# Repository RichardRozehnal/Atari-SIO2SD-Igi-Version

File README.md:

# Atari SIO2SD Igi Version

SIO2SD je zařízení, které vám umožní nahrávat programy a hry do Atari přes SIO konektor z SD/MMC karty.

## Seznam součástek:

| Ref                      | Qnty | Value                       | Cmp name                    |
|--------------------------|:----:|-----------------------------|-----------------------------|
| C1, C2,                  | 2    | 22pF                        | C_1206                      |
| C9, C8, C7, C6, C5, C4,  | 6    | 22nF                        | C_1206                      |
| C11, C13, C12,           | 3    | 10uF                        | C_Tantal_A/3216             |
| C14, C3, C10,            | 3    | 100nF                       | C_1206                      |
| D1,                      | 1    | LED_Zelená                  | LED_5mm_Zelená              |
| D2,                      | 1    | LED_Žlutá                   | LED_5mm_Žlutá               |
| D3,                      | 1    | LED_Červená                 | LED_5mm_Červená             |
| D4,                      | 1    | LL103A                      | LL103A                      |
| K1,                      | 1    | DRIVE                       | Mikrospínač_6x6x5mm         |
| K2,                      | 1    | NEXT                        | Mikrospínač_6x6x5mm         |
| K3,                      | 1    | CD..                        | Mikrospínač_6x6x5mm         |
| K4,                      | 1    | ENTER                       | Mikrospínač_6x6x5mm         |
| K5,                      | 1    | SHIFT                       | Mikrospínač_6x6x5mm         |
| K6,                      | 1    | RESET                       | Mikrospínač_6x6x5mm         |
| K7,                      | 1    | KF2510-5_Angled_Pitch2.54mm | KF2510-5_Angled_Pitch2.54mm |
| K8,                      | 1    | SD_Card                     | SD_Card                     |
| LCD1,                    | 1    | Display_16x2                | Display_16x2                |
| P1,                      | 1    | 5k                          | 3362P                       |
| R1, R3, R13,             | 3    | 10k                         | R_1206                      |
| R2,                      | 1    | 27R                         | R_1206                      |
| R4, R6, R5,              | 3    | 220R                        | R_1206                      |
| R9, R8, R7,              | 3    | 1k8                         | R_1206                      |
| R11, R12, R10,           | 3    | 3k3                         | R_1206                      |
| U1,                      | 1    | ATMEGA32A-AU                | ATMEGA32A-AU                |
| U2,                      | 1    | HT7533-1                    | HT7533-1                    |
| WP1,                     | 1    | MOSI                        | Wire_Pad                    |
| WP2,                     | 1    | MISO                        | Wire_Pad                    |
| WP3,                     | 1    | SCK                         | Wire_Pad                    |
| WP4,                     | 1    | RST                         | Wire_Pad                    |
| Y1,                      | 1    | 14.318MHz                   | Krystal_HC49-U_Vertical     |

## Fotky hotového výrobku (DPS verze 1):

## Původní autoři zařízení jsou:

Device inventor and AVR software developer: Jakub Kruszona-Zawadzki<br>
ATARI software developer and tester: Paweł Nowak (Pajero/MadTeam)<br>
NVC developer: Marcin Sochacki (Montezuma)<br>
Tester (also new SMD PCB designer - still not finished): Jakub Husak<br>

Tato verze má vylepšené a zjednodušené zapojení od [Igiho](http://blog.3b2.sk/igi/post/SIO2SD-3verzia.aspx).
Otestováno na Atari 800XE a vše funguje bez problému.

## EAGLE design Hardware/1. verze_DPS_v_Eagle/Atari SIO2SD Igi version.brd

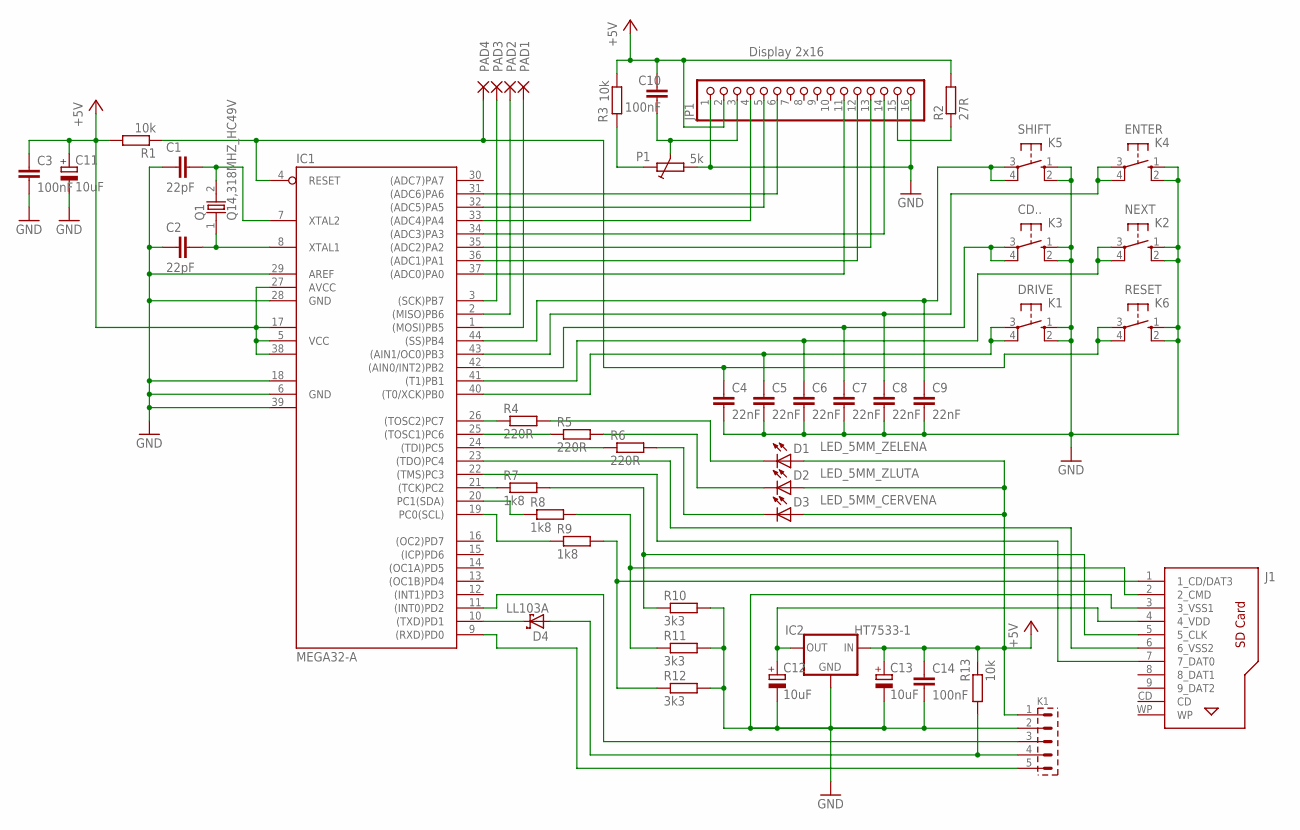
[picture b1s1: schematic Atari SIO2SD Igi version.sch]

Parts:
C1, C2: 22pF; 1206
C3, C10, C14: 100nF; 1206
C4, C5, C6, C7, C8, C9: 22nF; 1206
C11, C12, C13: 10uF; A/3216
CD..: K3; B3F-10XX
D1: LED_5MM_ZELENA; A5,0
D2: LED_5MM_ZLUTA; A5,0
D3: LED_5MM_CERVENA; A5,0
D4: LL103A; MINIMELF
DRIVE: K1; B3F-10XX
ENTER: K4; B3F-10XX
IC1: MEGA32-A; TQFP44
IC2: HT7533-1; SOT89R
J1: 693061010911
JP1: Display 2x16; 1X16
K1: PSH02-05W
NEXT: K2; B3F-10XX
P1: 5k; 3362P
PAD1, PAD2, PAD3, PAD4: SMD2; SMD1,27-2,54
Q1: Q14,318MHZ_HC49V; HC49U-V
R1, R3, R13: 10k; R1206
R2: 27R; R1206
R4, R5, R6: 220R; R1206
R7, R8, R9: 1k8; R1206
R10, R11, R12: 3k3; R1206
RESET: K6; B3F-10XX
SHIFT: K5; B3F-10XX

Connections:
+5V: C3.1, C10.1, C11.+, C13.+, C14.1, D1.A, D2.A, D3.A, IC1.5 (VCC), IC1.17 (VCC1), IC1.27 (AVCC), IC1.38 (VCC2), IC2.2 (IN), IC2.4 (IN), JP1.2, K1.1, R1.2, R2.2, R3.1, R13.2
GND: C1.1, C2.1, C3.2, C4.2, C5.2, C6.2, C7.2, C8.2, C9.2, C11.-, C12.-, C13.-, C14.2, CD...1 (S), CD...2 (S1), DRIVE.1 (S), DRIVE.2 (S1), ENTER.1 (S), ENTER.2 (S1), IC1.6 (GND), IC1.18 (GND1), IC1.28 (GND), IC1.29 (AREF), IC1.39 (GND2), IC2.1 (GND), J1.3 (3_VSS1), JP1.1, JP1.16, K1.2, NEXT.1 (S), NEXT.2 (S1), P1.A (1), R10.2, R11.2, R12.2, RESET.1 (S), RESET.2 (S1), SHIFT.1 (S), SHIFT.2 (S1)
unnamed: C1.2, IC1.7 (XTAL2), Q1.2
unnamed: C2.2, IC1.8 (XTAL1), Q1.1
unnamed: C10.2, JP1.3, P1.S (3)
unnamed: IC1.26 ((TOSC2)PC7), R4.1
unnamed: P1.E (2), R3.2
unnamed: C7.1, CD...3, CD...4 (P1), IC1.42 ((AIN0/INT2)PB2)
unnamed: IC1.31 ((ADC6)PA6), JP1.6
unnamed: JP1.15, R2.1
unnamed: IC1.32 ((ADC5)PA5), JP1.5
unnamed: IC1.33 ((ADC4)PA4), JP1.4
unnamed: IC1.34 ((ADC3)PA3), JP1.14
unnamed: IC1.35 ((ADC2)PA2), JP1.13
unnamed: IC1.36 ((ADC1)PA1), JP1.12
unnamed: IC1.37 ((ADC0)PA0), JP1.11
unnamed: C9.1, IC1.44 ((SS)PB4), SHIFT.3, SHIFT.4 (P1)
unnamed: C8.1, ENTER.3, ENTER.4 (P1), IC1.43 ((AIN1/OC0)PB3)
unnamed: IC1.25 ((TOSC1)PC6), R5.1
unnamed: C6.1, IC1.41 ((T1)PB1), NEXT.3, NEXT.4 (P1)
unnamed: C5.1, DRIVE.3, DRIVE.4 (P1), IC1.40 ((T0/XCK)PB0)
unnamed: C4.1, IC1.4 (RESET), PAD4.1, R1.1, RESET.3, RESET.4 (P1)
unnamed: IC1.24 ((TDI)PC5), R6.1
unnamed: D1.K (C), R4.2
unnamed: D2.K (C), R5.2
unnamed: D3.K (C), R6.2
unnamed: IC1.1 ((MOSI)PB5), PAD1.1
unnamed: IC1.23 ((TDO)PC4), J1.6 (6_VSS2)
unnamed: IC1.22 ((TMS)PC3), J1.7 (7_DAT0)
unnamed: IC1.21 ((TCK)PC2), R7.1
unnamed: IC1.20 (PC1(SDA)), R8.1
unnamed: IC1.19 (PC0(SCL)), R9.1
unnamed: J1.5 (5_CLK), R7.2, R10.1
unnamed: J1.2 (2_CMD), R8.2, R11.1
unnamed: J1.1 (1_CD/DAT3), R9.2, R12.1
unnamed: C12.+, IC2.3 (OUT), J1.4 (4_VDD)
unnamed: D4.C, IC1.10 ((TXD)PD1)
unnamed: D4.A, K1.4, R13.1
unnamed: IC1.11 ((INT0)PD2), K1.3
unnamed: IC1.9 ((RXD)PD0), K1.5
unnamed: IC1.2 ((MISO)PB6), PAD2.1
unnamed: IC1.3 ((SCK)PB7), PAD3.1

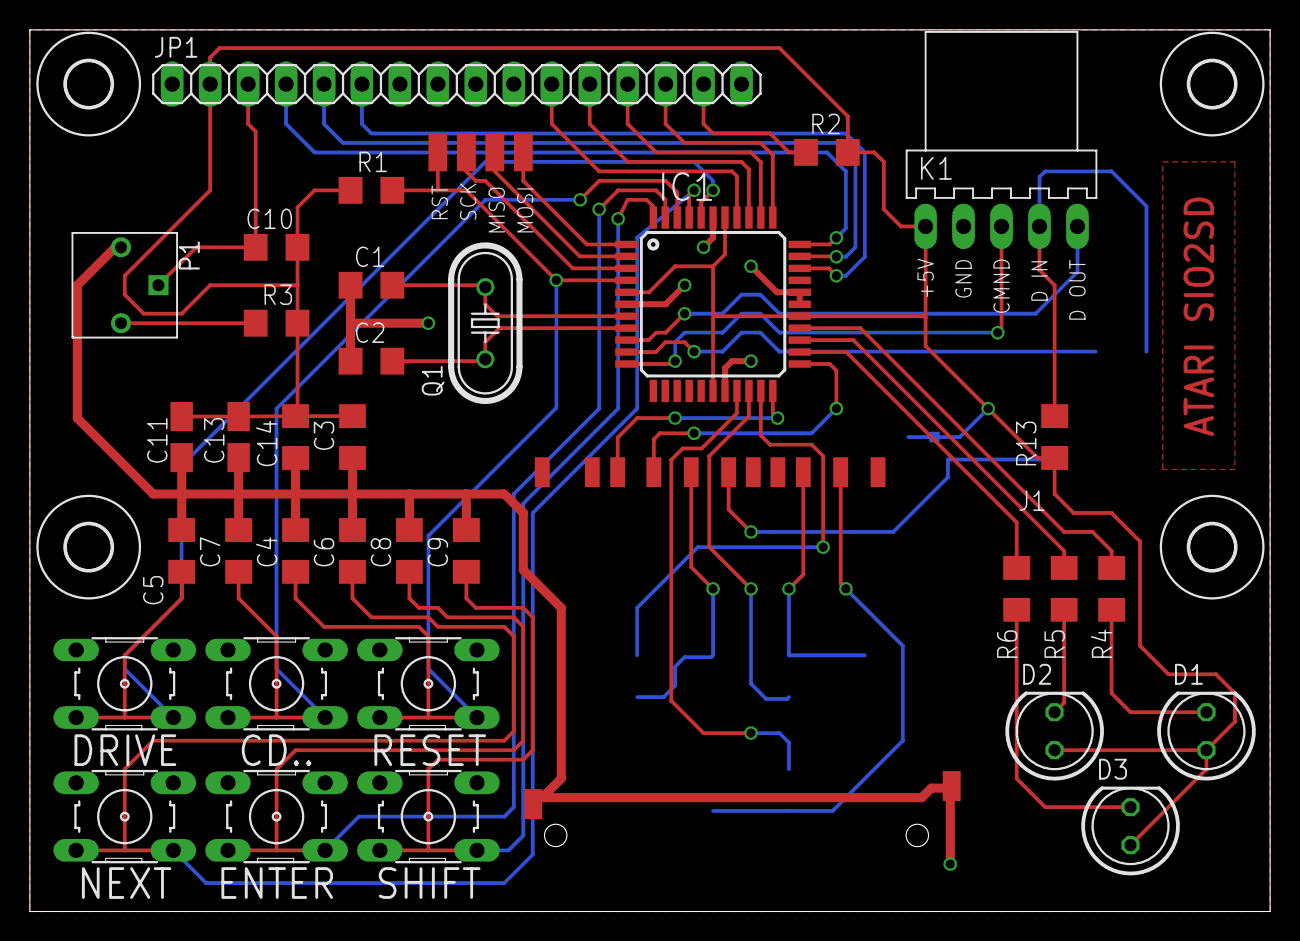
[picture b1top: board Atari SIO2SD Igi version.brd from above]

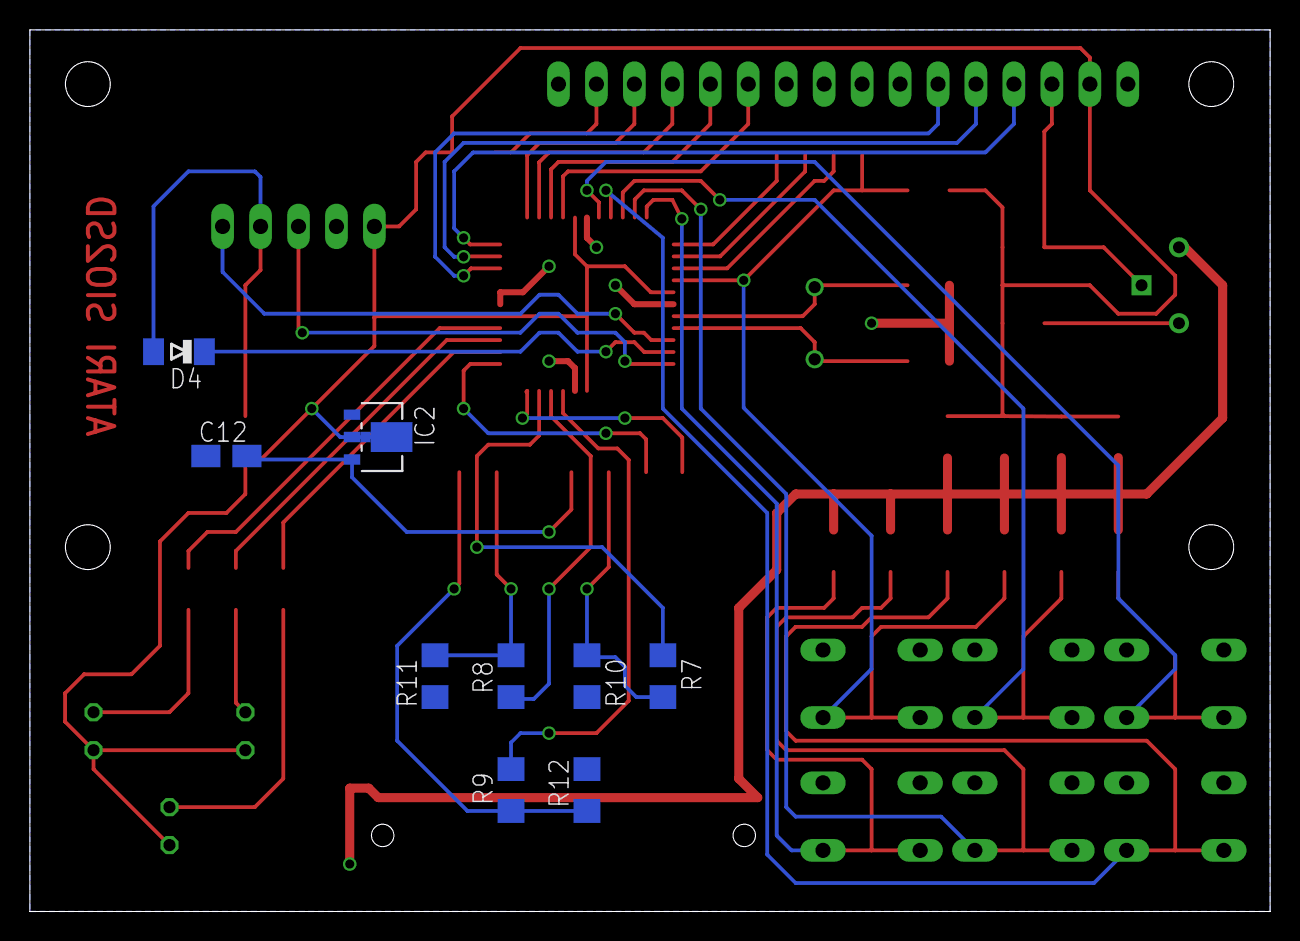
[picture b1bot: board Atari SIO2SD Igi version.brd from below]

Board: 2 copper layers, 83.0 x 59.0 mm, 52 parts (9 on the bottom side), 42 nets.

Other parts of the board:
U$1, U$2, U$3, U$4: 3,0

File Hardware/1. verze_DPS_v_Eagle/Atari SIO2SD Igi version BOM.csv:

"Qty";"Value";"Device";"Package";"Parts";"Description";"";
"1";"";"693063010911";"693063010911";"J1";"WR-CRD SD CARD CONNECTOR PUSH & PULL WITH CARD DETECTION 9PINS=>Code : Con_I-O_COM_CRD_SD_Normal_693063010911";"";
"1";"";"PSH02-05W";"PSH02-05W";"K1";"Konektory se zamkem - vidlice - 5pin";"";
"4";"";"SMD2";"SMD1,27-2,54";"PAD1, PAD2, PAD3, PAD4";"SMD PAD";"";
"3";"100nF";"C-SMD1206";"1206";"C3, C10, C14";"Kondenzátory keramické SMD 50 V";"";
"3";"10k";"R1206";"R1206";"R1, R3, R13";"Rezistor SMD 1206";"";
"3";"10uF";"CTSA";"A/3216";"C11, C12, C13";"Kondenzátory tantalové - SMD";"";
"3";"1k8";"R1206";"R1206";"R7, R8, R9";"Rezistor SMD 1206";"";
"3";"220R";"R1206";"R1206";"R4, R5, R6";"Rezistor SMD 1206";"";
"6";"22nF";"C-SMD1206";"1206";"C4, C5, C6, C7, C8, C9";"Kondenzátory keramické SMD 50 V";"";
"2";"22pF";"C-SMD1206";"1206";"C1, C2";"Kondenzátory keramické SMD 50 V";"";
"1";"27R";"R1206";"R1206";"R2";"Rezistor SMD 1206";"";
"3";"3k3";"R1206";"R1206";"R10, R11, R12";"Rezistor SMD 1206";"";
"1";"5k";"3362P";"3362P";"P1";"Odporové trimry 3362P";"";
"1";"BAT54S";"BAT54S";"SOT23";"D4";"Schottky";"";
"1";"Display 2x16";"PINHD-1X16";"1X16";"JP1";"PIN HEADER";"";
"1";"HT7533-1";"HT7533-1_SMD";"SOT89R";"IC2";"VOLTAGE REGULATOR";"";
"1";"K1";"10-XX";"B3F-10XX";"DRIVE";"OMRON SWITCH";"";
"1";"K2";"10-XX";"B3F-10XX";"NEXT";"OMRON SWITCH";"";
"1";"K3";"10-XX";"B3F-10XX";"CD..";"OMRON SWITCH";"";
"1";"K4";"10-XX";"B3F-10XX";"ENTER";"OMRON SWITCH";"";
"1";"K5";"10-XX";"B3F-10XX";"SHIFT";"OMRON SWITCH";"";
"1";"K6";"10-XX";"B3F-10XX";"RESET";"OMRON SWITCH";"";
"1";"LED_5MM_CERVENA";"LED_5MM_CERVENA";"A5,0";"D1";"LED 5mm";"";
"1";"LED_5MM_ZELENA";"LED_5MM_ZELENA";"A5,0";"D3";"LED 5mm";"";
"1";"LED_5MM_ZLUTA";"LED_5MM_ZLUTA";"A5,0";"D2";"LED 5mm";"";
"1";"MEGA32-A";"MEGA32-A";"TQFP44";"IC1";"MICROCONTROLLER";"";
"1";"Q14,318MHZ_HC49V";"Q14,318MHZ_HC49V";"HC49U-V";"Q1";"Krystal s pouzdrem HC-49U";"";

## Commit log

2019-08-10 Rename index.d to index.md
2019-08-10 Rename index.md to index.html
2019-08-10 Set theme jekyll-theme-cayman
2019-08-10 Rename index.html to index.md
2020-12-02 Create LICENSE

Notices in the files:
parts and their libraries:
Copyright (C) PaJa 2011-2014
